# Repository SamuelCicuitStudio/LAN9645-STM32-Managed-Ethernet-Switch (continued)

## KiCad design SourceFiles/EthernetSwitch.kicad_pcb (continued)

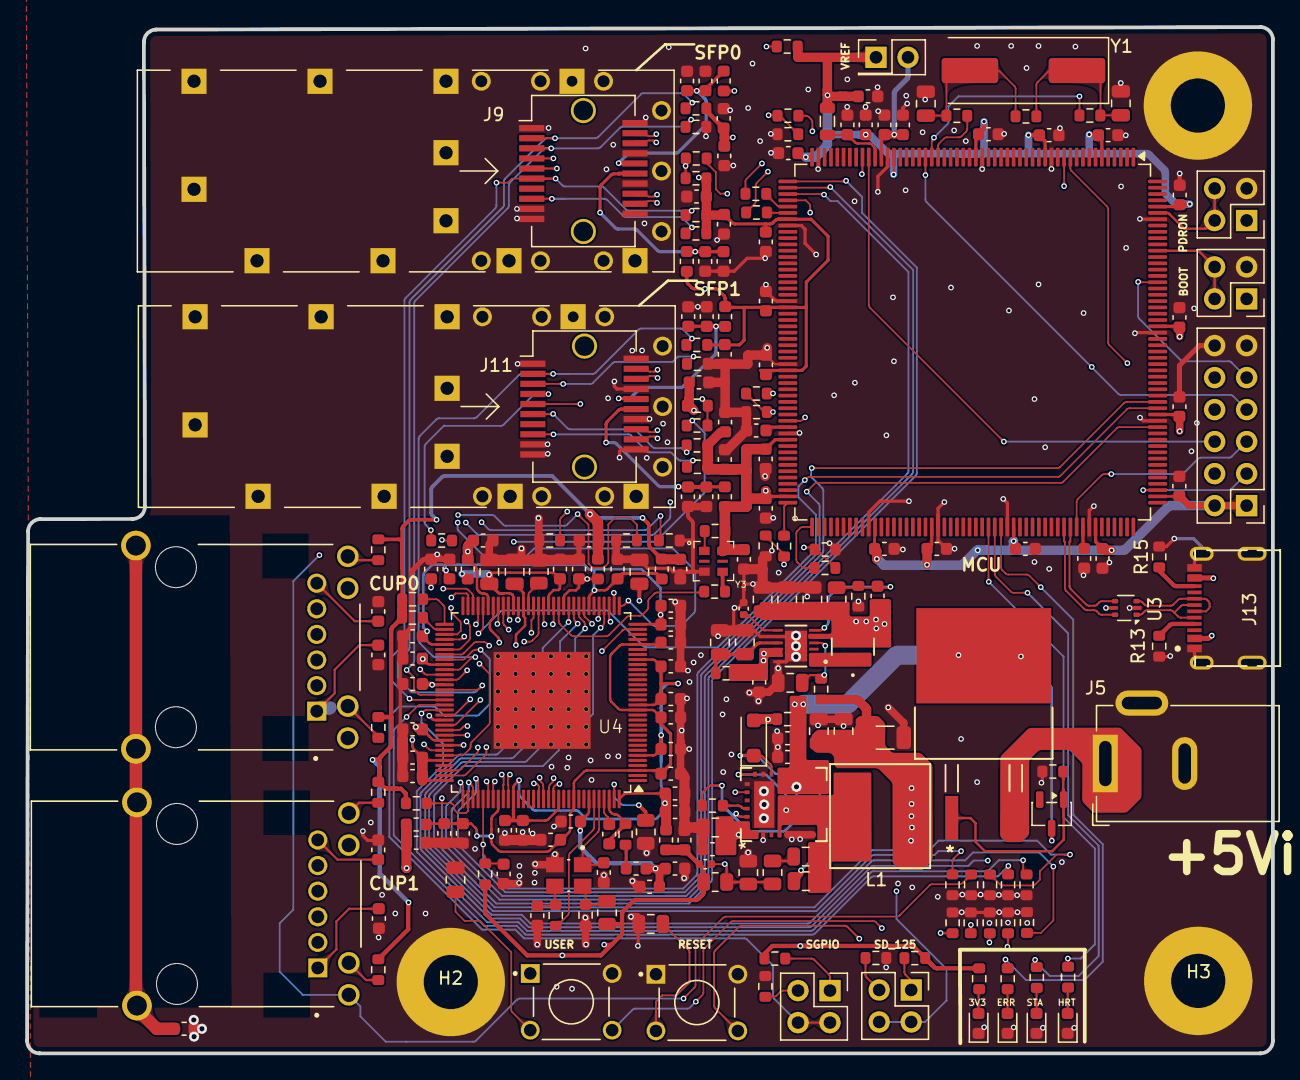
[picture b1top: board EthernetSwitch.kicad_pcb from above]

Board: 6 copper layers, 98.9 x 81.4 mm, 231 parts (0 on the bottom side), 150 nets.

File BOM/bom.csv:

Designator,Footprint,Quantity,Value,Part Number,Supplier Part Number 1,suplier
"C1, C10, C100, C101, C103, C104, C105, C108, C109, C11, C13, C14, C16, C18, C22, C24, C26, C27, C30, C31, C33, C35, C36, C37, C38, C40, C43, C48, C49, C5, C50, C52, C53, C54, C55, C57, C59, C60, C61, C62, C63, C65, C66, C67, C72, C73, C74, C79, C82, C83, C84, C85, C86, C87, C88, C89, C9, C90, C91, C94, C95, C96, C97, C98, C99",603,65,100nf,0603B472K500SD,3372-0603B472K500SDTR-ND,Digikey
"C102, C17, C20, C21, C28, C32, C46, C47, C58",805,9,100nf,0805B104K500BD,3372-0805B104K500BDTR-ND,Digikey
"C106, C107, C69, C70, C76, C77, C92, C93",603,8,10uF,0603W106M250XD,3372-0603W106M250XDTR-ND,Digikey
C19,0603,1,2.2uF,C1608X5R1C225K,445-5157-2-ND,Digikey
"C12, C15",603,2,2.2uF,0603W225K160XD,3372-0603W225K160XDTR-ND,Digikey
"C2, C25",603,2,1uF,0603B105K160XD,3372-0603B105K160XDTR-ND,Digikey
C23,402,1,4700pF,GRM155R71C472KA01D,490-6334-2-ND,Digikey
C29,1206,1,100uF,C3225X5R0J107M250AC,445-1437-2-ND,Digikey
"C3, C44, C45, C78, C8, C80, C81",603,7,4.7uF,C1608X5R1C475K080AC,445-7478-2-ND,Digikey
"C34, C75",805,1,10uF DNP,,,Digikey
"C39, C4, C51",805,3,1uF,0805B105K250CC,3372-0805B105K250CCTR-ND,Digikey
"C41, C56",603,2,15pF,GRM1555C1H150JA01D,490-5888-2-ND,Digikey
C42,402,1,10000pF,C0402C103K4RACTU,399-C0402C103K4RACTUCT-ND,Digikey
"C6, C7",805,2,20pF,0805N220J500AD,3372-0805N220J500ADTR-ND,Digikey
C64,603,1,33pF,GMC10CG330J50NT,4713-GMC10CG330J50NTTR-ND,Digikey
"C68, C71",805,2,22uF,C2012X5R1C226K,445-6797-2-ND,Digikey
D1,603,1,Led,NXL-1608UBC-04,5962-XL-1608UBC-04TR-ND,Digikey
D2,603,1,led,XL-1608SURC-06,5962-XL-1608SURC-06TR-ND,Digikey
D3,603,1,Led,XL-1608UGC-04,5962-XL-1608UGC-04TR-ND,Digikey
D4,603,1,Led,LTST-C170KFKT,160-1413-1-ND,Digikey
D5,D_SOD-123F,1,PMEG2010AEH,PMEG2010AEH,1727-3856-2-ND,Digikey
D6,SOT-23-3,1,BZX84C12,BZX84C12,2156-BZX84C12-488-ND,Digikey
FB1,805,1,220Ω@100MHz,BLM18EG221SN1D,490-3992-2-ND,Digikey
"FB10, FB11, FB15, FB4, FB5, FB6",603,6,"33 Ω @ 100 MHz, 3 A",MPZ2012S601AT000,445-MPZ2012S601AT000CT-ND,Digikey
"FB13, FB14, FB7, FB8",603,4,220 Ω,BLM18EG221SN1D,490-3992-2-ND,Digikey
FB2,603,1,600 Ω,HZ0603B102R-10,240-2378-2-ND,Digikey
"J1, J10, J12, J3",PinHeader_2x02_P2.54mm_Vertical,4,Conn_02x02_Row_Letter_Last,TSW-102-07-F-D,SAM10843-ND,Digikey
"J11, J9",Connector_SFP_and_Cage,2,SFP,U77-A1118-2001,664-U77A1118200TTR-ND,Digikey
J13,CONN_8p94X6p5X3p16_12L_GCC,1,USB4215-03-A,USB4215-03-A,2073-USB4215-03-ATR-ND,Digikey
J2,PinHeader_2x06_P2.54mm_Vertical,1,Conn_02x06_Row_Letter_Last,PH2-12-UA,2057-PH2-12-UA-ND,Digikey
J4,PinHeader_2x01_P2.54mm_Vertical,1,Conn_02x01_Row_Letter_First,TSW-102-07-F-S,SAM10844-ND,Digikey
J5,BarrelJack_GCT_DCJ200-10-A_Horizontal,1,Barrel_Jack_Switch,KLDX-0202-A-LT,2092-KLDX-0202-A-LT-ND,Digikey
"J6, J14","1 Port RJ45 Through Hole 10/100 Base-T, AutoMDIX",2,RJ45,08B0-1X1T-36-F,5923-08B0-1X1T-36-F-ND,Digikey
L1,IND_XAL7070_COC,1,XAL7070-682MEC,XAL7070-682MEC,XAL7070-682MEC,Digikey
L2,IND_TAIYO_NR3015_TAY,1,NR3015T1R0N,NR3015T1R0N,587-1647-1-ND,Digikey
Q1,TRAN_IRF4905STRLPBF_INF,1,IRF4905STRLPBF,IRF4905STRLPBF,IRF4905STRLPBFTR-ND,Digikey
"R1, R2, R39, R40, R41, R42, R43, R44, R49, R50, R51, R52, R53, R54, R55, R58, R62, R63, R64, R65, R67, R70, R71, R8, R9",603,25,1kΩ,CR0603-FX-1001ELF,CR0603-FX-1001ELFCT-ND,Digikey
R10,805,1,19.1kΩ,CR0805-FX-1912ELF,118-CR0805-FX-1912ELFTR-ND,Digikey
R11,805,1,8.2kΩ 1%,CR0805-FX-8201ELF,118-CR0805-FX-8201ELFTR-ND,Digikey
R12,805,1,2.61kΩ 1%,CR0805-FX-2611ELF,118-CR0805-FX-2611ELFTR-ND,Digikey
R45,0805,,DNP,,,
"R13, R15",603,2,5.1kΩ,CR0603-FX-5101ELF,CR0603-FX-5101ELFTR-ND,Digikey
"R14, R3, R36, R37, R48, R59, R60, R61, R66, R68, R72, R73, R74, R75, R76",603,15,10kΩ,CR0603-FX-1002ELF,CR0603-FX-1002ELFCT-ND,Digikey
"R16, R17, R18",603,3,3.3KΩ,CR0603-FX-3301ELF,CR0603-FX-3301ELFTR-ND,Digikey
"R19, R46",603,2,10Ω,CR0603-FX-10R0ELF,CR0603-FX-10R0ELFTR-ND,Digikey
"R20, R21, R22, R23, R24, R25, R26, R27, R28, R69",603,10,22Ω,CR0603-FX-22R0ELF,118-CR0603-FX-22R0ELFTR-ND,Digikey
R29,805,1,200Ω@1%,CR0805-FX-2000ELF,118-CR0805-FX-2000ELFCT-ND,Digikey
R30,805,1,6kΩ@1%,CR0805-FX-6041ELF,118-CR0805-FX-6041ELFTR-ND,Digikey
R31,603,1,100kΩ,CR0603-FX-1003ELF,CR0603-FX-1003ELFCT-ND,Digikey
"R32, R33, R34, R35",603,4,470Ω,CR0603-FX-4700ELF,CR0603-FX-4700ELFTR-ND,Digikey
"R38, R4, R47, R6, R7",603,5,0Ω,CR0603-J/-000ELF,CR0603-J/-000ELFTR-ND,Digikey
R5,603,1,10MΩ,CR0603-FW-1005ELF,CR0603-FW-1005ELFTR-ND,Digikey
R56,805,1,232kΩ,CR0805-FX-2323ELF,118-CR0805-FX-2323ELFTR-ND,Digikey
R57,603,1,270kΩ,CR0603-FX-2703ELF,CR0603-FX-2703ELFTR-ND,Digikey
"SW1, SW2",SW_1825910-6-4,2,1825910-6,1825910-6,450-1650-ND,Digikey
U1,LQFP-208_28x28mm_P0.5mm,1,STM32H743BIT6,STM32H743BIT6,497-18562-ND,Digikey
U2,QFN28_5X6_MCH,1,MIC24051YJL-TR,MIC24051YJL-TR,576-4282-2-ND,Digikey
U3,SOT-666,1,USBLC6-2P6,USBLC6-2P6,497-5026-2-ND,Digikey
U4,128-TQFP,1,LN96459,LN96459,150-LAN96459S-I/8NW-ND,Digikey
U5,DFN12_3X3_ML_MCH,1,MIC23303YML-TR,MIC23303YML-TR,150-MIC23303YML-TR-ND,Digikey
Y1,Crystal_SMD_HC49-SD,1,8Mhz,XH8M000000S420,3372-XH8M000000S420TR-ND,Digikey
Y2,XTAL_ABM8G-25.000MHZ-B4Y-T,1,ABM8G-25.000MHZ-B4Y-T,ABM8G-25.000MHZ-B4Y-T,535-10297-2-ND,Digikey
Y3,6-VDFN,1,DSC1101BI2-125.0000,DSC1101BI2-125.0000,150-DSC1101BI2-125.0000-ND,Digikey

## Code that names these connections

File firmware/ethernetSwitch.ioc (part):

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Mcu.Name=STM32H743BITx
Mcu.Package=LQFP208
Mcu.UserName=STM32H743BITx
PA0.Mode=Asynchronous
PA0.Signal=UART4_TX
PA1.Mode=RMII
PA1.Signal=ETH_REF_CLK
PA11.Mode=Device_Only
PA11.Signal=USB_OTG_FS_DM
PA12.Mode=Device_Only
PA12.Signal=USB_OTG_FS_DP
PA13\ (JTMS/SWDIO).Mode=Serial_Wire
PA13\ (JTMS/SWDIO).Signal=DEBUG_JTMS-SWDIO
PA14\ (JTCK/SWCLK).Mode=Serial_Wire
PA14\ (JTCK/SWCLK).Signal=DEBUG_JTCK-SWCLK
PA2.Mode=RMII
PA2.Signal=ETH_MDIO
PA4.GPIOParameters=GPIO_Label
PA4.GPIO_Label=SPI_NSS
PA4.Signal=GPIO_Output
PA5.Mode=Full_Duplex_Master
PA5.Signal=SPI1_SCK
PA6.Mode=Full_Duplex_Master
PA6.Signal=SPI1_MISO
PA7.Mode=RMII
PA7.Signal=ETH_CRS_DV
PB11.Mode=RMII
PB11.Signal=ETH_TX_EN
PB12.Mode=RMII
PB12.Signal=ETH_TXD0
PB13.Mode=RMII
PB13.Signal=ETH_TXD1
PC1.Mode=RMII
PC1.Signal=ETH_MDC
PC13.Mode=Calibration_1Hz
PC13.Signal=RTC_OUT_CALIB
PC4.Mode=RMII
PC4.Signal=ETH_RXD0
PC5.Mode=RMII
PC5.Signal=ETH_RXD1
PD5.GPIOParameters=GPIO_Label
PD5.GPIO_Label=LAN RST
PD5.Signal=GPIO_Output
PD6.GPIOParameters=GPIO_Label
PD6.GPIO_Label=IRQ0
PD6.Signal=GPXTI6
PD7.Mode=Full_Duplex_Master
PD7.Signal=SPI1_MOSI
PG6.GPIOParameters=GPIO_Label
PG6.GPIO_Label=HEART
PG6.Signal=GPIO_Output
PG7.GPIOParameters=GPIO_Label
PG7.GPIO_Label=STATUS
PG7.Signal=GPIO_Output
PG8.GPIOParameters=GPIO_Label
PG8.GPIO_Label=ERR
PG8.Signal=GPIO_Output
PH0-OSC_IN\ (PH0).Mode=HSE-External-Oscillator
PH0-OSC_IN\ (PH0).Signal=RCC_OSC_IN
PH1-OSC_OUT\ (PH1).Mode=HSE-External-Oscillator
PH1-OSC_OUT\ (PH1).Signal=RCC_OSC_OUT
PI10.GPIOParameters=GPIO_Label
PI10.GPIO_Label=USR
PI10.Signal=GPIO_Input
PI9.Mode=Asynchronous
PI9.Signal=UART4_RX
RCC.HSE_VALUE=8000000
RCC.SYSCLKFreq_VALUE=96000000
RCC.SYSCLKSource=RCC_SYSCLKSOURCE_PLLCLK
board=custom

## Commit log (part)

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2026-04-04 Initial project import with LAN9645 pin assignment docs
2026-04-04 Update LAN9645 strap plan for external 125MHz SerDes clock control
2026-04-04 Refine LAN9645 managed RMII strap plan and full bootstrap classification
2026-04-04 Clarify managed-mode bootstrap usage and pin states
2026-04-04 Add LAN9645 managed bring-up and ping test configuration guide
2026-04-04 Add LAN9645 design docs and STM32H743 LwIP firmware base
2026-04-04 Reorganize reference PDFs and add KiCad backup artifacts
2026-04-04 Finalize LAN9645 managed spec and sync firmware config updates
2026-04-04 Clarify CLI error routing and debug serial ownership
2026-04-04 docs: lock LAN9645 comm error routing to USB/UART debug line
2026-04-04 docs: split Design into hardware and firmware docs
2026-04-04 docs+fw: add generated bring-up checklist and sync current config
2026-04-04 docs: add USER_PHY spec and library implementation plan
2026-04-05 docs: lock library API dependencies and align implementation plan
2026-04-05 docs: phase-lock implementation plan with register-map freeze
2026-04-05 Implement LAN9645 bring-up stack, USER_PHY integration, CLI ingress, and docs updates
2026-04-05 Import LAN9645x BSP sources and update SPI findings
2026-04-05 docs: complete LAN9645 STM32 BSP sequencing guides
2026-04-05 Implement LAN9645 bring-up diagnostics and CLI runtime checks
2026-04-05 Add Doxygen comments to custom public headers
2026-04-05 Add Doxygen comments to custom source files
2026-04-05 Lock precise BSP feature roadmap and close ETH MSP/cache software setup
2026-04-05 Add SPI transport telemetry and CLI stats commands
2026-04-05 Close F1 with SPI error diagnostics and status-all telemetry
2026-04-05 Implement F2 port admin/mode APIs with CLI and diag reporting
2026-04-05 Implement F3 VLAN baseline service and CLI vlan commands
2026-04-05 Add LAN9645 SYS counter service and CLI cnt commands
2026-04-05 Implement F5 IRQ cause-action contract and checked ACK flow
2026-04-05 Freeze CLI result envelope contract for baseline commands
2026-04-05 Finalize F7 traceability matrix and hardware backlog closure
2026-04-05 Add Linux feature matrix control layer and CLI feature commands
2026-04-05 Expand feature matrix with AFI and manual injection baseline
2026-04-05 Remove Design/firmware/lan9645x reference driver folder
2026-04-05 Document project handbook and expand LAN9645 firmware baseline
2026-04-05 Expand root handbook with detailed LAN9645 and CLI docs
2026-04-05 Add full firmware debug output tree
